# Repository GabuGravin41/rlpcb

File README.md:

# RL PCB — an AI design copilot for KiCad

RL PCB sits beside KiCad and works like a senior hardware engineer looking over your shoulder. You describe
what you want to build; it helps you choose real parts from your KiCad libraries, works out the values, places
the symbols for you, tells you **exactly** which pin connects to which pin, and then **checks your wiring**.
It also helps with the board: stackup, net classes, placement, routing guidance, autorouting and DRC.

**The division of labour is deliberate:** language models are bad at drawing schematics (floating "ghost"
wires, near-misses), so RL PCB never draws wires. You draw, and it does everything around the drawing:
research, parts, numbers, placement, instructions, and verification.

```
 you ──► "I need a 24 V PLC input card with 8 isolated inputs"
          │
 RL PCB ─►│ requirements → architecture → datasheet/app-note research → reference designs
          │ → parts from YOUR libraries → calculated values → design plan (parts + nets)
          │ → plan review (ERC before drawing) → symbols placed (no wires)
          │ → "wire U3 pin 7 (OUT) to R12 pin 1 …" → you wire → verify: 87 % done,
          │   R14.2 not connected, ghost wire at (120.6, 88.9) mm → fix → 100 %
          │ → stackup + net classes → placement → routing guidance / autoroute → DRC → Gerbers
```

## You choose how much the AI does

The engineer sets the AI's autonomy for each part of the design:

- **teach:** it explains.
- **advise:** it guides; you edit.
- **propose:** it prepares each change on a copy of the project, with the check results before and after, and you
  accept or reject it.
- **do:** it edits; every change is journalled and can be undone.

For example, the power block can be in "do" while the routing is in "advise". Every result says what the checks
verified and what they could not, such as part data without a datasheet or EMC that was not simulated, so a weaker
model's mistakes are caught where checks exist and flagged where they do not. See `docs/COPILOT.md`.

| Copilot tool | What it does |
|---|---|
| `copilot_status`, `copilot_mode` | Show or set the modes and scopes. |
| `proposals`, `proposal_show`, `proposal_accept`, `proposal_reject` | Review changes prepared on a copy. The chat panel has a Proposals button. |
| `undo`, `design_journal` | History of who changed what, in which mode; any change can be undone. |
| `assurance_report` | What is verified and what is not, before you order boards. |
| `kickoff`, `kickoff_apply` | From an idea to an architecture, questions, pitfalls and a project skeleton. |
| `explain_component`, `explain_net` | What a part or net does in this circuit, and why it is there. |
| `review_layout`, `compare_layouts` | Placement, routing, EMC and current-capacity review (IPC-2221 track widths against the plan's currents) with reasons; side-by-side layout studies. |
| `widen_power_tracks` | Widens the tracks of current-carrying nets as far as KiCad's DRC allows. |
| `interface_changes` | Notices between this board and the mechanical design (RL CAD). |

## What's inside

| Area | What it does |
|---|---|
| **Connectivity engine** | Computes nets from the drawing itself (pins, wires, junctions, labels, power symbols, hierarchical sheets, buses incl. bus aliases). Validated against KiCad's own netlister: **identical nets on all 13 KiCad 7 demo projects**, and on the KiCad 9/10 demos (Jetson Thor carrier, CM5, VME) it matches the boards' own netlists apart from stale/mechanical items. Reads KiCad 4/5 `.sch` too. |
| **Ghost-wire detector** | Dangling wire ends (with "near-miss: meant for U3 pin 7, 0.6 mm away"), floating wire groups, wire ends on the middle of another wire without a junction (KiCad treats these as *not connected*), labels touching nothing, off-grid pins, shorted power nets, misused no-connect flags. |
| **Library index** | SQLite/FTS search over every symbol and footprint in your KiCad libraries (stock + global + project tables, KiCad 7–10 incl. `.kicad_symdir`). Pins, footprint filters, pad counts, pitch. The AI never invents a part name. |
| **Design plan** | The agreed circuit (parts + nets + no-connects + requirements + decisions), stored in `<project>/.rlpcb/plan.json`. Pins can be named (`U1.VIN`, `U2.GND` → all GND pins, `U1.GPIO20` finds `IO20`). |
| **Plan review** | ERC for intent before drawing: unconnected power pins, floating inputs, output conflicts, missing decoupling, symbol/footprint pin-count mismatches. |
| **Symbol placement** | Groups each IC with the passives that serve it and lays them out around the pins they connect to (decoupling next to VCC, pull-up next to the output…), packs the groups on the sheet, grid-aligned, value & footprint set — **no wires**. Clipboard mode (Ctrl+V into the open editor) or file mode (with backups). Hierarchical sheets per block (`add_sheet`). Optional net labels exactly on pin ends for wide buses. |
| **Parts from anywhere** | Stock/global/project libraries; LCSC/JLCPCB parts converted on the fly (`import_lcsc_part C2040` → symbol + footprint + 3D, LCSC field set); symbols borrowed from open designs in the corpus; datasheets downloaded into the knowledge base (`fetch_datasheet`). |
| **Manufacturing** | Gerbers/drill/positions/STEP via kicad-cli; JLCPCB BOM + CPL (`export_jlcpcb`); plan fields (MPN, LCSC, voltage…) written back into drawn symbols (`sync_fields_from_plan`). |
| **Circuit blocks** | Pre-verified sub-circuits (buck, LDO, battery input, ADC divider, STM32F405 core, IMU, barometer, SPI flash, USB-C device, LED, connectors) with calculated values. MCUs connect by *function* (`SPI1_SCK`, `USART1_TX`, `USB_DP`) — the block knows the pins and refuses conflicts. The drone board rebuilt from 16 blocks verifies at 100 % with KiCad agreeing on every net. |
| **Design checks** | Engineering review beyond ERC: MCU pin functions, USB-C CC/data wiring, STM32 VCAP, TVS orientation, pin role vs net (swapped regulators), LED polarity, cap voltage ratings, inductor current, missing pull-ups, back-feed between supplies, nets that go nowhere, board fit; on the PCB: decoupling distance, crystal distance, track width vs current. |
| **Guided flow** | `next_step` reads the project and returns the single next action (with the exact tool call) plus a checklist — so smaller models (and beginners) don't get lost. |
| **Multi-board systems** | `system.json` with boards and harnesses: every cable pin pair checked (ground/power/voltage/TX↔RX/driver conflicts/open pins/pin count/per-pin current) plus the supply budget across boards. |
| **Wiring guide** | Per net: shortest wiring order (minimum spanning tree over the real pin coordinates), power symbols for rails, labels for far-apart pins, done/not-done per step. |
| **Verification** | Hand-drawn schematic vs plan: progress %, missing connections, shorts between planned nets, unplanned connections, wrong values/footprints, unplaced units, plus ghost wires. |
| **See the drawing** | Renders sheets to images and "pulls up" any section: zoomed crop around `U3, R7` with red highlight boxes. |
| **PCB tools** | Board overview & routing progress, stackup advisor (layer count from BGA pitch/interfaces/rails), net classes from the plan written into `.kicad_pro`, custom DRC rules, placement suggestions with target coordinates for every small passive (decoupling one cap per supply pin, pull-ups/load caps at their pin, two-sided, collision-free), footprint moves and flips (live or file), DRC, fabrication outputs. |
| **Routing** | Guidance by net class; Freerouting autorouting round-trip (DSN → router → SES, with a pure-Python SES importer) into a *copy* of your board; live track/via creation through the KiCad API for agreed simple routes. |
| **Live KiCad API** | KiCad 9/10 IPC API (kicad-python): highlight parts, read the selection, move footprints in one undo step, add tracks/vias, refill zones. |
| **Knowledge base** | ~35 dense engineering guides (power, decoupling/PDN, buck/boost, LDOs, BMS/UPS, high current, PLC I/O, motor drives, analog, EMC, stackups, SI, USB/Ethernet/PCIe/DDR, BGA & GPU-class boards, MCU/FPGA, RF, aerospace/high-rel, printers, DFM, KiCad workflow), 10 industry reference architectures (PLC, elevator, conveyor, humanoid joint, UPS, load sharing, printer mainboard, GPU accelerator, avionics, IoT), review/bring-up/fab checklists — plus **your own PDFs/books/datasheets** (`ingest_documents`). |
| **Reference corpus** | Ingests open-source KiCad projects (KiCad demos, GitHub repos, your folders; KiCad 4–10) and learns *how real designs wire each IC*: "how do others wire the DRV8302?" returns every pin's net and neighbours in the VESC design, with a consensus across designs. Seed list: Jetson Orin/Nano & Kria carriers, VESC, LibreSolar BMS/MPPT, LumenPnP, HackRF, Cynthion… |
| **Calculators** | IPC-2221 trace width, trace/via resistance & current, microstrip/stripline/differential impedance + width solver, critical length, skew, IPC-2221 clearance, E-series, feedback dividers, LED, RC, crystal load caps, buck/boost power stage, LDO thermal, MOSFET loss, PDN target impedance, capacitor SRF, shunts, thermal vias, wavelength. Every result shows the formula and caveats. |

## Three ways to talk to it

1. **Claude Desktop (works with your Claude Pro plan — no API key).** The installer registers RL PCB as an
   MCP server; open Claude Desktop and all 90 tools are available. Say *"Open my KiCad project in
   Documents\KiCad\myboard and help me design…"*.
2. **The RL PCB panel inside KiCad.** A toolbar button (PCB editor; also the schematic editor on KiCad 10)
   opens a chat panel. It needs either an Anthropic API key (Settings ⚙) or a local model through any
   OpenAI-compatible server (Ollama, LM Studio…).
3. **Claude Code / any MCP client:** `claude mcp add rlpcb -- <venv python> -m rlpcb.agent.mcp_server`.

## Install (Windows)

Requirements: KiCad 8, 9 or 10 (9/10 recommended), Python 3.10+, Git (for the corpus), optionally Java 21 for
autorouting.

```powershell
cd path\to\rlpcb
powershell -ExecutionPolicy Bypass -File .\install_windows.ps1            # add -SeedCorpus to download reference designs
```

It creates `.venv`, installs `mcp`, `kicad-python`, `pymupdf`, indexes your libraries, installs the KiCad
plugins into `Documents\KiCad\<version>\`, registers with Claude Desktop, makes a desktop shortcut, then runs
`python -m rlpcb doctor`.

Then in KiCad 9/10: **Preferences → Plugins → Enable KiCad API** (for live highlighting and moves) and restart.

Linux/macOS: `./install.sh [--seed-corpus]`.

## First session

```
You:     Open C:\Users\me\Documents\KiCad\plc_input and let's design an 8-channel 24 V digital input card
         for a Raspberry Pi CM5, IEC 61131-2 type 1, galvanically isolated.
RL PCB:  (asks about channel count, isolation voltage, connectors, power) … proposes architecture …
         searches the knowledge base (industrial_plc_io) and reference designs … calculates the input
         divider/current limiter … builds the plan … plan_review: 0 errors …
         places 41 symbols (Ctrl+V) … "Block 'input_ch1': 1) Draw a wire from J1 pin 1 at (25.4, 40.6) to
         R1 pin 1 at (38.1, 40.6) …"
You:     done with channel 1
RL PCB:  verify → 92 %: R3 pin 2 is not connected; the wire from U2 pin 3 ends 0.64 mm short of it
         (dangling end at 120.65, 88.90). Everything else in channel 1 matches the plan.
```

## Command line

```
python -m rlpcb doctor                    # check everything
python -m rlpcb index [--force]           # (re)index libraries
python -m rlpcb check  path\to\project    # ghost wires & drawing problems
python -m rlpcb verify path\to\project    # schematic vs plan
python -m rlpcb nets   path\to\project [regex]
python -m rlpcb ingest-docs D:\Books\Electronics
python -m rlpcb corpus seed | owner/repo | D:\OpenHardware
python -m rlpcb tool <tool_name> '{"json": "args"}'
python -m rlpcb serve --open              # chat panel
python -m rlpcb mcp                       # MCP server (stdio)
```

## Safety of your files

- Schematic/board edits are *splices*: the rest of the file stays byte-for-byte identical, the result is parsed
  before writing, and a timestamped backup goes to `<project>\.rlpcb\backups\`.
- If KiCad has the file open (lock file present), RL PCB warns you; clipboard mode and the live API avoid the
  conflict entirely.
- The autorouter writes `<name>.routed.kicad_pcb`, never your original.
- `mech_export` writes `<board>.mech.json`, which describes the board for the product around it: outline, holes, connectors with the edge they face, and part heights. `mech_check` checks the board against the `enclosure.json` that RL CAD writes. See `../rlcad/docs/INTEGRATION.md`.
- `finish_routing` closes what the autorouter left (plane stitching, grid router, rip-up, negotiated congestion) and writes `<name>.finished.kicad_pcb`, checked with KiCad's own DRC after every step.
- The panel server only listens on 127.0.0.1 and rejects cross-origin requests. `allow_file_writes=false` in
  Settings makes RL PCB read-only.

## Honest limits (and the roadmap)

- It will not draw wires, by design. Net labels on pin ends are offered for buses.
- The AI's design judgement is only as good as its research: it cites the knowledge base, the datasheet section
  and real reference designs, and you should still read the datasheet's typical-application circuit.
- Autorouting is for non-critical nets; power loops, high-speed and analog nets should be routed by hand with
  the guidance given.
- A Blackwell-class accelerator board (20+ layer HDI, ~1000 A core rail, PCIe Gen5/6) is not a first project;
  the `gpu_accelerator_board` architecture file lays out a realistic learning path toward it.

See `docs/EVALUATION.md` for how a small model performs with and without blocks, `examples/drone_fc/` for a complete worked project (a drone flight controller, idea → routed board), `docs/USER_GUIDE.md` for the workflow in depth and `docs/ARCHITECTURE.md` for how it works.

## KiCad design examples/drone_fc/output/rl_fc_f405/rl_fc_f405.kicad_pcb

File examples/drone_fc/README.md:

# Worked example: a drone flight controller, from idea to routed board

This is what a new project looks like with RL PCB. Every step below is a real tool call. `design_session.py`
and `board_session.py` are the exact sequence the copilot runs, so you can replay it.

**Brief:** a 5-inch-quad flight controller, 36×36 mm, 30.5 mm M3 mounting, 2–6S LiPo input, Betaflight-style pinout.

| Stage | What RL PCB did | Result |
|---|---|---|
| Requirements → architecture | Recorded requirements + decisions in the plan: STM32F405 (the Betaflight/INAV reference MCU), TPS5430 buck 5 V/3 A → AP2112K 3.3 V LDO, IMU on its own ferrite-filtered rail, SIG/GND/PWR/SIG stackup | `.rlpcb/plan.json` |
| Parts | 61 parts, all from the stock KiCad libraries (symbol + footprint pin counts checked) | 0 invented parts |
| Numbers | Feedback divider 9.31 k/3.01 k → 4.998 V; crystal loads 2·(12−3) = 18 pF; VBAT divider 10 k/1 k → 25.2 V reads 2.29 V; buck L ≈ 13.4 µH → 15 µH, Isat > 3 A | shown with formulas |
| Plan review (ERC before drawing) | Power pins, floating inputs, output conflicts, decoupling, no-connects | **0 errors, 0 warnings** |
| Placement (schematic) | 4 hierarchical sheets (Power / MCU / Sensors / Connectors); each IC placed with its passives beside the pins they serve. **No wires.** | `img/1_schematic_mcu_sheet.png` |
| Wiring guide | Per net: power symbols for rails, global labels for nets that cross sheets, shortest wire order for the rest (e.g. *"Draw a wire from U1.8 (PH) at (78.74, 45.72) to C3.2 at (93.98, 40.64)"*) | step list |
| Verify | Hand-drawn schematic vs plan | 100 % of 174 connections; KiCad's own netlister agrees (79/79 nets) |
| Mistake detection | Swapped SDA/SCL on the baro, and a label dropped 0.64 mm short of a pin | *"Planned nets I2C1_SCL, I2C1_SDA are connected together…"*, *"global label 'SPI1_MISO' is not attached…; nearest pin is U4.4 (SAO/SD0) 0.64 mm away"* |
| Stackup + net classes | 4 layers (density 5 parts/cm², USB 90 Ω); 6 net classes, 32 patterns written to `.kicad_pro` | |
| Board placement | You (or the copilot) place ~20 anchor parts from the plan's layout notes; `placement_suggestions` puts the 40 passives next to the pins they serve (MCU decoupling one cap per VDD pin, load caps at the crystal, pull-ups at the pin), 22 parts on the bottom side | 0 courtyard overlaps; a second pass is a no-op |
| Autoroute (Freerouting, 3 min) | Routes a *copy* of the board | 88–91 % routed across runs, 0 clearance errors from routing; 17–22 connections left for you |
| DRC | Remaining errors are all footprint-inherent: 0.5 mm-pitch LGA pads vs the 0.2 mm default clearance (set Default clearance to 0.15 mm, since JLC allows 0.1), the USB-C's own NPTH tabs, and one via 0.03 mm too close to the edge | |

## What *you* still do (by design)

1. **Draw the wires.** RL PCB never draws them. Follow the wiring guide, then say "verify".
2. **Press F8** (Update PCB from Schematic). In the cloud demo, `make_board.py` stands in for F8.
3. **Route the critical nets by hand before autorouting:** the buck hot loop (C1–U1–D1), the switch node,
   USB D+/D−, and the IMU SPI. Then lock them, autoroute the rest, and finish the last ~10 % by hand.
4. **Read the datasheet sections the copilot points at.** In this design:
   - ICM-20602 RESV pins: the symbol marks them reserved, but check the datasheet for any that must be tied to GND or VDDIO.
   - SMAJ28A: this library symbol names its pins A1/A2, so the plan uses pin numbers. Confirm the cathode faces VBAT.
   - SRP7028A-150M: confirm Isat ≥ 3 A. (L1 was downsized from a 12.5 mm part so it fits on a 36 mm board.)
   - USB-only power: 5 V can back-feed the VBAT rail through the TPS5430 high-side body diode when no battery is
     connected. Many flight controllers accept this; add a diode or load switch if your ESC must stay unpowered.

## Finishing the board (fabrication-ready)

The autorouted copy above still had open connections, so the board was finished for manufacture:

1. **Design rules set for JLCPCB 4-layer**: 0.13 mm default clearance (0.15 mm power/analog, 0.2 mm VBAT), 0.15 mm
   signal tracks, 0.4 mm power, 1.0 mm VBAT, 0.6/0.3 mm vias (0.5/0.3 mm around the IMU), 0.3 mm copper-to-edge.
2. **Freerouting with In1 (GND) and In2 (+3V3) as planes only**: the bottom GND pour was left out of the router's
   input, because the router treated it as a plane and left bottom-side GND pads "connected" to islands that do not
   exist once KiCad fills the pour. Three passes (14 + 8 + 7 min on 2 cores) left 5 connections.
3. **`rlpcb.pcb.finish`** (new) closed the rest with KiCad's own geometry and DRC after every step:
   plane stitching (stub + via from a pad to its plane), a 4-layer grid router with vias, rip-up and retry, and a
   negotiated-congestion router (PathFinder-style) for the two knots: the IMU's SPI fan-out under the MCU, and the
   BMP280 corner. Dangling stubs and an edge-violating via were removed; the USB-C shield pads connect solid.

Result (`output/rl_fc_f405/rl_fc_f405.kicad_pcb`, KiCad DRC): **0 errors, 0 unconnected pads**, 239 pad-to-net
assignments identical to the plan. Remaining warnings: 52 silkscreen overlaps, 22 silk over copper, 2 silk at the
board edge (cosmetic; the fab clips silk on pads), and library-path notices from the machine it was routed on.
52 short segments run on the inner plane layers (24 on In1, 28 on In2). Check the GND return path under the IMU SPI
lines if you care about the last dB of noise.

### Power-stage rework after the layout review

`review_layout` later found real problems in the routed board above, which DRC could not see because they are about
current and loop area, not spacing:

- **Switch node:** the buck's switch node (BUCK_SW, 2.5 A) was 22 mm of 0.15 mm track that wound under the
  regulator. At that current, IPC-2221 puts the rise at roughly 250 °C, and the long loop radiates. The cause was
  that `setup_netclasses` sized nets only by their declared class, so a switch node with a current but no class got
  the 0.15 mm default. It now sizes every net that has a current.
- **+5V rail:** the 2 A rail ran 0.4 mm on the inner layers. Part of it ran on In1 (the GND plane), which also cut
  the ground plane.

The rework, done with RL PCB's own tools (placement, grid router, `widen_power_tracks`, KiCad DRC after each step):

- U1 is turned 180°, so its PH pin faces the catch diode and the inductor. L1 moves 0.85 mm left.
- The switch node is now one 6 × 9 mm copper pour joining U1 PH, the bootstrap capacitor, D1 and L1.
- The input capacitor C1 sits at the VIN pin, with its ground in a small pour tied to the regulator's thermal pad
  and the planes.
- The feedback divider (R1, R2) moves next to the FB pin. It senses the output through a thin trace.
- C5 (22 µF) moves under L1's output as the buck's output capacitor; C4 stays at the LDO.
- +5V leaves the inner layers. A 1.0 mm trunk runs on B.Cu to the LDO and receiver corner, and a 0.8 mm branch runs
  to the VTX connector.
- The rest of the +5V and VBAT copper is widened as far as DRC allows.

After the rework, `review_layout` reports no power concerns (it had three). DRC is still 0 errors and 0 unconnected
pads, and the Gerbers, drill, positions, STEP, CPL and `mech.json` are regenerated.

Two points are left for the engineer:

- **USB pair length mismatch (10.4 mm):** this stays as it is. USB_DP and USB_DM leave the ESD clamp in the opposite
  order to the one in which they arrive at the MCU, so routing them side by side needs a crossing. At USB full speed
  (12 Mb/s, the F405's OTG_FS) this mismatch does not affect the data. The clean fix is a schematic change: swap the
  clamp's two channels (USBLC6-2 channels are interchangeable), then route both lines together.
- **VBAT width:** the plan gives VBAT 3 A, which leaves its 1.0 mm tracks at about 17 °C rise. The board itself draws
  well under 2 A from the battery, so check the plan's figure before widening further.

Manufacturing files are in `output/rl_fc_f405/fab/`: Gerbers + drill (+ drill map) for the 4 copper layers,
`positions.csv`, and `jlcpcb/` BOM + CPL with LCSC numbers. Five BOM lines have no LCSC number on purpose:
J1 (battery pads) and J6 (SWD pads) are not assembled; L1 (SRP7028A-150M), R2 (3.01 k 1 %) and Y1 (8 MHz 3225,
CL = 12 pF to match the 18 pF load caps) must be picked at order time or supplied.

## Replay it

```bash
python examples/drone_fc/design_session.py  C:\work            # plan, review, sheets, placement, wiring guide
python examples/drone_fc/design_session.py  C:\work --labels   # demo only: simulate a finished drawing
# open C:\work\rl_fc_f405 in KiCad, wire it (or use --labels), press F8, save
python examples/drone_fc/board_session.py   C:\work\rl_fc_f405 --route
```

Or just ask in the chat panel / Claude Desktop: *"Design a 30.5 mm flight controller with an F405, ICM-20602,
BMP280, blackbox flash and a 2–6S input"*. The copilot runs these same tools and stops to ask you at each decision.

## The generated project

`output/rl_fc_f405/` is the result of the replay, saved in KiCad 7 format (KiCad 8/9/10 upgrade it when you open it).
It contains:

- the 4-sheet schematic with pin labels (the simulated drawing);
- `rl_fc_f405.kicad_pcb`, the finished, routed board (DRC clean);
- `rl_fc_f405.placed.kicad_pcb`, the placed board before routing;
- `fab/`, the manufacturing files;
- `.rlpcb/plan.json`, the design plan, so you can open the project and ask RL PCB about any part or net.

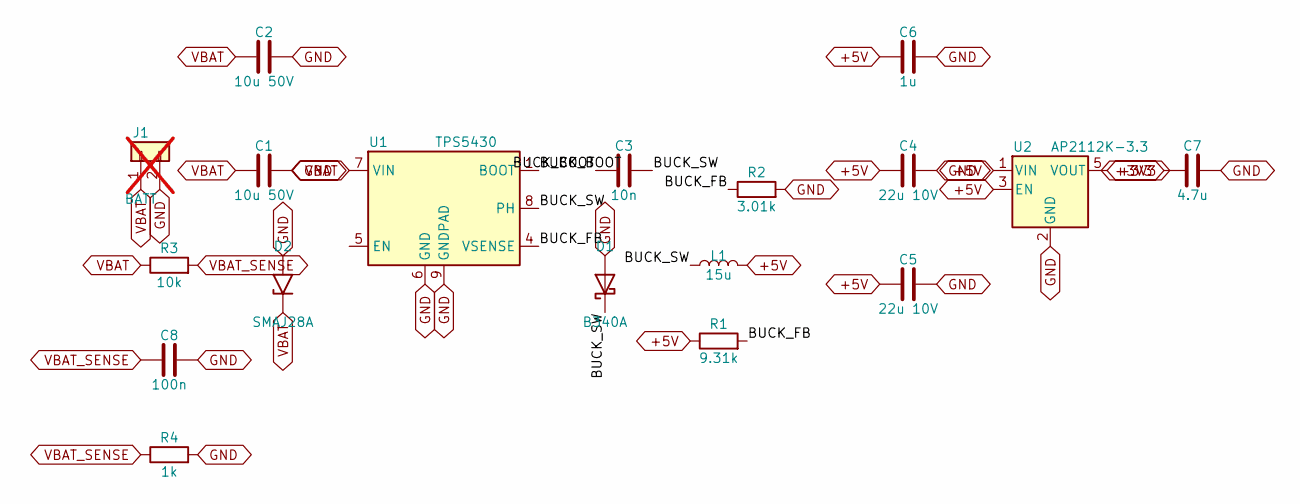
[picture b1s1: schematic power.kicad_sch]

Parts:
C1, C2: 10u 50V; C_1206_3216Metric; MPN CL31A106KBHNNNE; LCSC C13585
C3: 10n; C_0402_1005Metric; MPN CL05B103KB5NNNC; LCSC C15195
C4, C5: 22u 10V; C_0805_2012Metric; MPN CL21A226MAQNNNE; LCSC C45783
C6: 1u; C_0402_1005Metric; MPN CL05A105KA5NQNC; LCSC C52923
C7: 4.7u; C_0603_1608Metric; MPN CL10A475KO8NNNC; LCSC C19666
C8: 100n; C_0402_1005Metric; MPN CL05B104KO5NNNC; LCSC C1525
D1: B340A; D_SMA; MPN B340A-13-F; LCSC C85098
D2: SMAJ28A; D_SMA; MPN SMAJ28A-13-F; LCSC C134977
J1: BATT; SolderWire-1.5sqmm_1x02_P6mm_D1.7mm_OD3mm; not fitted
L1: 15u; L_Bourns_SRP7028A_7.3x6.6mm; MPN SRP7028A-150M
R1: 9.31k; R_0402_1005Metric; MPN RNCF0402BKE9K31; LCSC C4174801
R2: 3.01k; R_0402_1005Metric
R3: 10k; R_0402_1005Metric; MPN 0402WGF1002TCE; LCSC C25744
R4: 1k; R_0402_1005Metric; MPN 0402WGF1001TCE; LCSC C11702
U1: TPS5430; TI_SO-PowerPAD-8_ThermalVias; MPN TPS5430DDAR; LCSC C9864
U2: AP2112K-3.3; SOT-23-5; MPN AP2112K-3.3TRG1; LCSC C51118

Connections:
+3V3: C7.1, U2.5 (VOUT); also elsewhere on the board
+5V: C4.1, C5.1, C6.1, L1.2, R1.1, U2.1 (VIN), U2.3 (EN); also elsewhere on the board
/Power/BUCK_BOOT: C3.1, U1.1 (BOOT)
/Power/BUCK_FB: R1.2, R2.1, U1.4 (VSENSE)
/Power/BUCK_SW: C3.2, D1.1 (K), L1.1, U1.8 (PH)
GND: C1.2, C2.2, C4.2, C5.2, C6.2, C7.2, C8.2, D1.2 (A), D2.2 (A2), J1.2, R2.2, R4.2, U1.6 (GND), U1.9 (GNDPAD), U2.2 (GND); also elsewhere on the board
VBAT: C1.1, C2.1, D2.1 (A1), J1.1, R3.1, U1.7 (VIN); also elsewhere on the board
VBAT_SENSE: C8.1, R3.2, R4.1; also elsewhere on the board

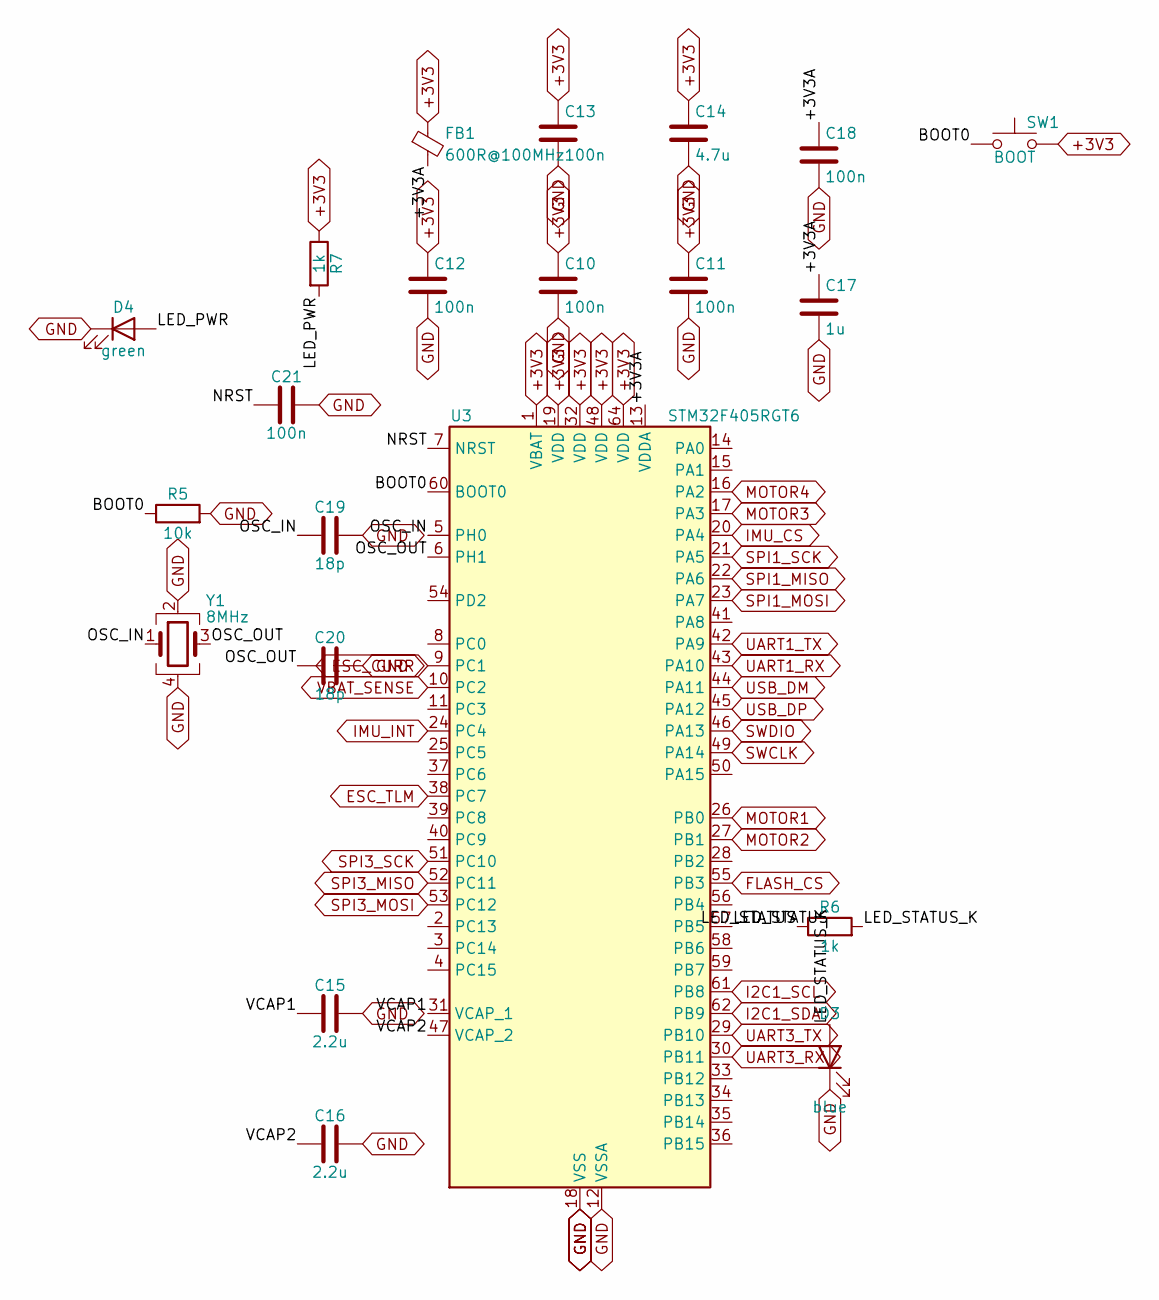
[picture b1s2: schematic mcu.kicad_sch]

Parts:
C10, C11, C12, C13, C18, C21: 100n; C_0402_1005Metric; MPN CL05B104KO5NNNC; LCSC C1525
C14: 4.7u; C_0603_1608Metric; MPN CL10A475KO8NNNC; LCSC C19666
C15, C16: 2.2u; C_0402_1005Metric; MPN CL05A225MQ5NSNC; LCSC C12530
C17: 1u; C_0402_1005Metric; MPN CL05A105KA5NQNC; LCSC C52923
C19, C20: 18p; C_0402_1005Metric; MPN 0402CG180J500NT; LCSC C1549
D3: blue; LED_0603_1608Metric; MPN KT-0603B; LCSC C2288
D4: green; LED_0603_1608Metric; MPN KT-0603G; LCSC C12624
FB1: 600R@100MHz; L_0603_1608Metric; MPN GZ1608D601TF; LCSC C1002
R5: 10k; R_0402_1005Metric; MPN 0402WGF1002TCE; LCSC C25744
R6, R7: 1k; R_0402_1005Metric; MPN 0402WGF1001TCE; LCSC C11702
SW1: BOOT; SW_SPST_TL3342; MPN TL3342F160QG; LCSC C2886898
U3: STM32F405RGT6; LQFP-64_10x10mm_P0.5mm; MPN STM32F405RGT6; LCSC C15742
Y1: 8MHz; Crystal_SMD_3225-4Pin_3.2x2.5mm

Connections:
+3V3: C10.1, C11.1, C12.1, C13.1, C14.1, FB1.1, R7.1, SW1.2, U3.1 (VBAT), U3.19 (VDD), U3.32 (VDD), U3.48 (VDD), U3.64 (VDD); also elsewhere on the board
/MCU/+3V3A: C17.1, C18.1, FB1.2, U3.13 (VDDA)
/MCU/BOOT0: R5.1, SW1.1, U3.60 (BOOT0)
/MCU/LED_PWR: D4.2 (A), R7.2
/MCU/LED_STATUS: R6.1, U3.57 (PB5)
/MCU/LED_STATUS_K: D3.2 (A), R6.2
/MCU/NRST: C21.1, U3.7 (NRST)
/MCU/OSC_IN: C19.1, U3.5 (PH0), Y1.1
/MCU/OSC_OUT: C20.1, U3.6 (PH1), Y1.3
/MCU/VCAP1: C15.1, U3.31 (VCAP_1)
/MCU/VCAP2: C16.1, U3.47 (VCAP_2)
ESC_CURR: U3.9 (PC1); also elsewhere on the board
ESC_TLM: U3.38 (PC7); also elsewhere on the board
FLASH_CS: U3.55 (PB3); also elsewhere on the board
GND: C10.2, C11.2, C12.2, C13.2, C14.2, C15.2, C16.2, C17.2, C18.2, C19.2, C20.2, C21.2, D3.1 (K), D4.1 (K), R5.2, U3.12 (VSSA), U3.18 (VSS), U3.63 (VSS), Y1.2, Y1.4; also elsewhere on the board
I2C1_SCL: U3.61 (PB8); also elsewhere on the board
I2C1_SDA: U3.62 (PB9); also elsewhere on the board
IMU_CS: U3.20 (PA4); also elsewhere on the board
IMU_INT: U3.24 (PC4); also elsewhere on the board
MOTOR1: U3.26 (PB0); also elsewhere on the board
MOTOR2: U3.27 (PB1); also elsewhere on the board
MOTOR3: U3.17 (PA3); also elsewhere on the board
MOTOR4: U3.16 (PA2); also elsewhere on the board
SPI1_MISO: U3.22 (PA6); also elsewhere on the board
SPI1_MOSI: U3.23 (PA7); also elsewhere on the board
SPI1_SCK: U3.21 (PA5); also elsewhere on the board
SPI3_MISO: U3.52 (PC11); also elsewhere on the board
SPI3_MOSI: U3.53 (PC12); also elsewhere on the board
SPI3_SCK: U3.51 (PC10); also elsewhere on the board
SWCLK: U3.49 (PA14); also elsewhere on the board
SWDIO: U3.46 (PA13); also elsewhere on the board
UART1_RX: U3.43 (PA10); also elsewhere on the board
UART1_TX: U3.42 (PA9); also elsewhere on the board
UART3_RX: U3.30 (PB11); also elsewhere on the board
UART3_TX: U3.29 (PB10); also elsewhere on the board
USB_DM: U3.44 (PA11); also elsewhere on the board
USB_DP: U3.45 (PA12); also elsewhere on the board
VBAT_SENSE: U3.10 (PC2); also elsewhere on the board

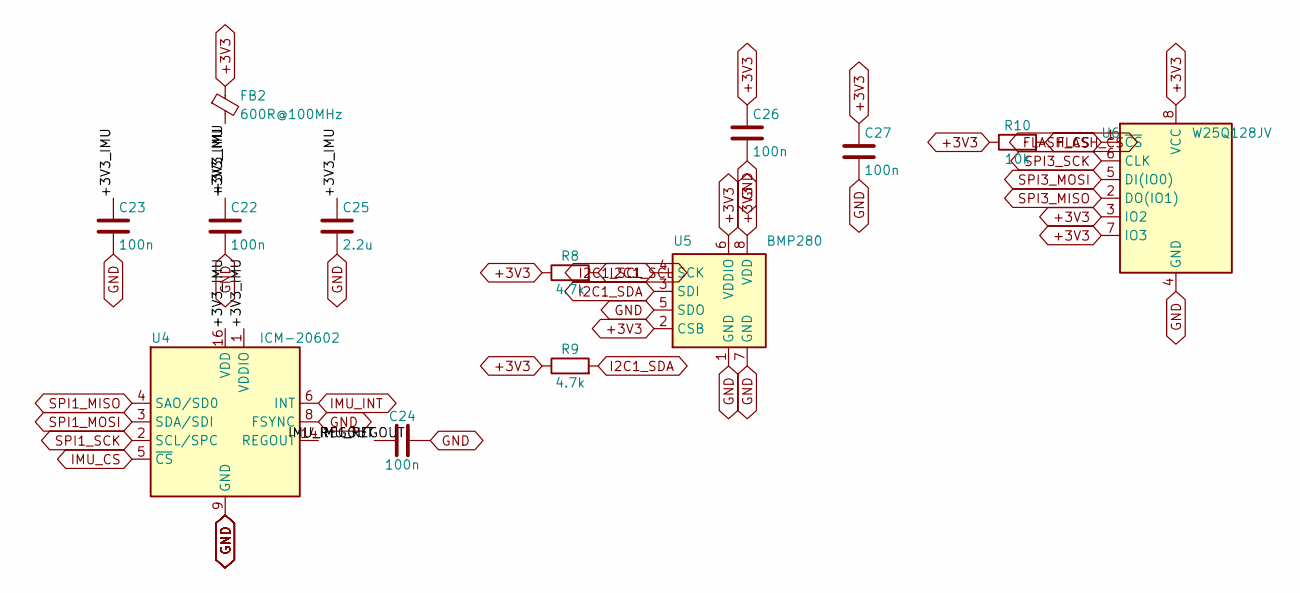
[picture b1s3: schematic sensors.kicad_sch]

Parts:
C22, C23, C24, C26, C27: 100n; C_0402_1005Metric; MPN CL05B104KO5NNNC; LCSC C1525
C25: 2.2u; C_0402_1005Metric; MPN CL05A225MQ5NSNC; LCSC C12530
FB2: 600R@100MHz; L_0603_1608Metric; MPN GZ1608D601TF; LCSC C1002
R8, R9: 4.7k; R_0402_1005Metric; MPN 0402WGF4701TCE; LCSC C25900
R10: 10k; R_0402_1005Metric; MPN 0402WGF1002TCE; LCSC C25744
U4: ICM-20602; LGA-16_3x3mm_P0.5mm_LayoutBorder3x5y; MPN ICM-20602; LCSC C97633
U5: BMP280; Bosch_LGA-8_2x2.5mm_P0.65mm_ClockwisePinNumbering; MPN BMP280; LCSC C83291
U6: W25Q128JV; SOIC-8_5.23x5.23mm_P1.27mm; MPN W25Q128JVSIQ; LCSC C97521

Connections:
+3V3: C26.1, C27.1, FB2.1, R8.1, R9.1, R10.1, U5.2 (CSB), U5.6 (VDDIO), U5.8 (VDD), U6.3 (IO2), U6.7 (IO3), U6.8 (VCC); also elsewhere on the board
/Sensors/+3V3_IMU: C22.1, C23.1, C25.1, FB2.2, U4.1 (VDDIO), U4.16 (VDD)
/Sensors/IMU_REGOUT: C24.1, U4.14 (REGOUT)
FLASH_CS: R10.2, U6.1 (~CS); also elsewhere on the board
GND: C22.2, C23.2, C24.2, C25.2, C26.2, C27.2, U4.8 (FSYNC), U4.9 (GND), U4.10 (GND), U4.11 (GND), U4.12 (GND), U4.13 (GND), U4.15 (GND), U5.1 (GND), U5.5 (SDO), U5.7 (GND), U6.4 (GND); also elsewhere on the board
I2C1_SCL: R8.2, U5.4 (SCK); also elsewhere on the board
I2C1_SDA: R9.2, U5.3 (SDI); also elsewhere on the board
IMU_CS: U4.5 (~CS); also elsewhere on the board
IMU_INT: U4.6 (INT); also elsewhere on the board
SPI1_MISO: U4.4 (SAO/SD0); also elsewhere on the board
SPI1_MOSI: U4.3 (SDA/SDI); also elsewhere on the board
SPI1_SCK: U4.2 (SCL/SPC); also elsewhere on the board
SPI3_MISO: U6.2 (DO(IO1)); also elsewhere on the board
SPI3_MOSI: U6.5 (DI(IO0)); also elsewhere on the board
SPI3_SCK: U6.6 (CLK); also elsewhere on the board

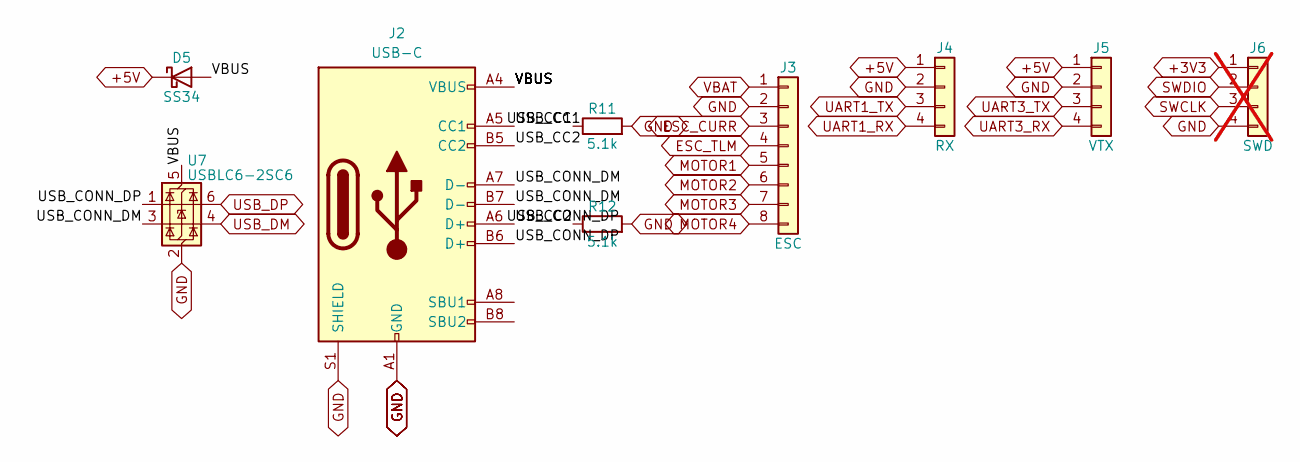
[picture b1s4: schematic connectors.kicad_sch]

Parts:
D5: SS34; D_SMA; MPN SS34; LCSC C8678
J2: USB-C; USB_C_Receptacle_GCT_USB4105-xx-A_16P_TopMnt_Horizontal; MPN USB4105-GF-A; LCSC C3020560
J3: ESC; JST_SH_SM08B-SRSS-TB_1x08-1MP_P1.00mm_Horizontal; MPN SM08B-SRSS-TB(LF)(SN); LCSC C160407
J4: RX; JST_SH_SM04B-SRSS-TB_1x04-1MP_P1.00mm_Horizontal; MPN SM04B-SRSS-TB(LF)(SN); LCSC C160404
J5: VTX; JST_SH_SM04B-SRSS-TB_1x04-1MP_P1.00mm_Horizontal; MPN SM04B-SRSS-TB(LF)(SN); LCSC C160404
J6: SWD; PinHeader_1x04_P1.27mm_Vertical; not fitted
R11, R12: 5.1k; R_0402_1005Metric; MPN 0402WGF5101TCE; LCSC C25905
U7: USBLC6-2SC6; SOT-23-6; MPN USBLC6-2SC6; LCSC C7519

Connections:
+3V3: J6.1; also elsewhere on the board
+5V: D5.1 (K), J4.1, J5.1; also elsewhere on the board
/Connectors/USB_CC1: J2.A5 (CC1), R11.1
/Connectors/USB_CC2: J2.B5 (CC2), R12.1
/Connectors/USB_CONN_DM: J2.A7 (D-), J2.B7 (D-), U7.3 (I/O2)
/Connectors/USB_CONN_DP: J2.A6 (D+), J2.B6 (D+), U7.1 (I/O1)
/Connectors/VBUS: D5.2 (A), J2.A4 (VBUS), J2.A9 (VBUS), J2.B4 (VBUS), J2.B9 (VBUS), U7.5 (VBUS)
ESC_CURR: J3.3; also elsewhere on the board
ESC_TLM: J3.4; also elsewhere on the board
GND: J2.A1 (GND), J2.A12 (GND), J2.B1 (GND), J2.B12 (GND), J2.S1 (SHIELD), J3.2, J4.2, J5.2, J6.4, R11.2, R12.2, U7.2 (GND); also elsewhere on the board
MOTOR1: J3.5; also elsewhere on the board
MOTOR2: J3.6; also elsewhere on the board
MOTOR3: J3.7; also elsewhere on the board
MOTOR4: J3.8; also elsewhere on the board
SWCLK: J6.3; also elsewhere on the board
SWDIO: J6.2; also elsewhere on the board
UART1_RX: J4.4; also elsewhere on the board
UART1_TX: J4.3; also elsewhere on the board
UART3_RX: J5.4; also elsewhere on the board
UART3_TX: J5.3; also elsewhere on the board
USB_DM: U7.4 (I/O2); also elsewhere on the board
USB_DP: U7.6 (I/O1); also elsewhere on the board
VBAT: J3.1; also elsewhere on the board

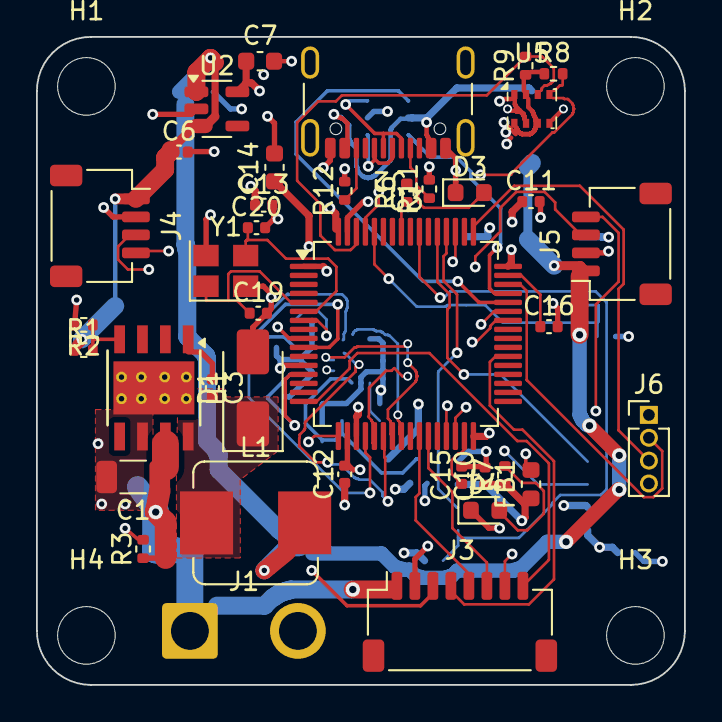
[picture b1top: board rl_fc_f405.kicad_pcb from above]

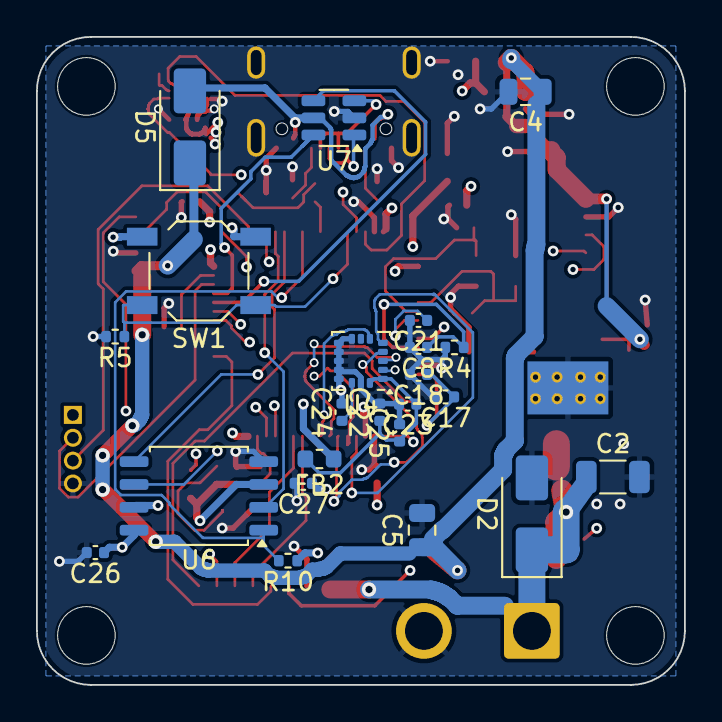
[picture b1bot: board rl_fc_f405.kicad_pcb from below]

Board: 4 copper layers, 36.0 x 36.0 mm, 65 parts (23 on the bottom side), 50 nets.

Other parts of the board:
H1, H2, H3, H4: MountingHole_3.2mm_M3

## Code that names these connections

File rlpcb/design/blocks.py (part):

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A block is a parameterised sub-circuit whose internal wiring, part choices and values have been checked once (against
the datasheet's typical application and by building a board with it). A model using blocks only chooses blocks, sets a
few parameters and connects *ports* — e.g. ``{"VOUT": "+5V", "GND": "GND"}``, or for an MCU peripheral functions
such as ``{"SPI1_SCK": "IMU_SCK", "USART1_TX": "RX_TX"}`` instead of pin numbers. That removes most of the places a
weaker model can go wrong: pin names, decoupling, feedback networks, crystal loads, alternate-function pins.

Every block returns the calculations it made (with formulas) and the datasheet points a human should still confirm.
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# =============================================================================== MCU
# STM32F405RGTx: default alternate-function pin for each peripheral signal (LQFP-64).
F405_FUNCTIONS = {
    "USB_DM": "PA11", "USB_DP": "PA12", "SWDIO": "PA13", "SWCLK": "PA14",
    "SPI1_SCK": "PA5", "SPI1_MISO": "PA6", "SPI1_MOSI": "PA7",
    "SPI2_SCK": "PB13", "SPI2_MISO": "PB14", "SPI2_MOSI": "PB15",
    "SPI3_SCK": "PC10", "SPI3_MISO": "PC11", "SPI3_MOSI": "PC12",
    "I2C1_SCL": "PB8", "I2C1_SDA": "PB9", "I2C2_SCL": "PB10", "I2C2_SDA": "PB11",
    "USART1_TX": "PA9", "USART1_RX": "PA10", "USART2_TX": "PA2", "USART2_RX": "PA3",
    "USART3_TX": "PB10", "USART3_RX": "PB11", "UART4_TX": "PA0", "UART4_RX": "PA1",
    "USART6_TX": "PC6", "USART6_RX": "PC7",
    "TIM3_CH1": "PB4", "TIM3_CH2": "PB5", "TIM3_CH3": "PB0", "TIM3_CH4": "PB1",
    "TIM5_CH3": "PA2", "TIM5_CH4": "PA3", "TIM8_CH1": "PC6", "TIM8_CH2": "PC7", "TIM4_CH1": "PB6", "TIM4_CH2": "PB7",
    "CAN1_RX": "PB8", "CAN1_TX": "PB9",
    "ADC_IN0": "PA0", "ADC_IN1": "PA1", "ADC_IN4": "PA4", "ADC_IN8": "PB0", "ADC_IN9": "PB1",
    "ADC_IN10": "PC0", "ADC_IN11": "PC1", "ADC_IN12": "PC2", "ADC_IN13": "PC3", "ADC_IN14": "PC4", "ADC_IN15": "PC5",
}
# Every pin that can carry each function on the STM32F405 LQFP-64 (datasheet AF table, common peripherals).
F405_AF = {
    "USB_DP": {"PA12"}, "USB_DM": {"PA11"}, "SWDIO": {"PA13"}, "SWCLK": {"PA14"},
    "SPI1_SCK": {"PA5", "PB3"}, "SPI1_MISO": {"PA6", "PB4"}, "SPI1_MOSI": {"PA7", "PB5"},
    "SPI2_SCK": {"PB10", "PB13"}, "SPI2_MISO": {"PB14", "PC2"}, "SPI2_MOSI": {"PB15", "PC3"},
    "SPI3_SCK": {"PC10", "PB3"}, "SPI3_MISO": {"PC11", "PB4"}, "SPI3_MOSI": {"PC12", "PB5"},
    "I2C1_SCL": {"PB6", "PB8"}, "I2C1_SDA": {"PB7", "PB9"}, "I2C2_SCL": {"PB10"}, "I2C2_SDA": {"PB11"},
    "I2C3_SCL": {"PA8"}, "I2C3_SDA": {"PC9"},
    "USART1_TX": {"PA9", "PB6"}, "USART1_RX": {"PA10", "PB7"}, "USART2_TX": {"PA2"}, "USART2_RX": {"PA3"},
    "USART3_TX": {"PB10", "PC10"}, "USART3_RX": {"PB11", "PC11"}, "UART4_TX": {"PA0", "PC10"}, "UART4_RX": {"PA1", "PC11"},
    "UART5_TX": {"PC12"}, "UART5_RX": {"PD2"}, "USART6_TX": {"PC6"}, "USART6_RX": {"PC7"},
    "CAN1_RX": {"PB8", "PA11"}, "CAN1_TX": {"PB9", "PA12"}, "CAN2_RX": {"PB5", "PB12"}, "CAN2_TX": {"PB6", "PB13"},
}
# generic net-name tokens → the set of function names that satisfy them
F405_GENERIC = {
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}
MCU_AF = {"MCU_ST_STM32F4:STM32F405RGTx": (F405_AF, F405_GENERIC)}

F405_GPIO = [f"P{b}{i}" for b, n in (("A", 16), ("B", 16), ("C", 16)) for i in range(n)] + ["PD2", "PH0", "PH1"]
F405_RESERVED = {"PH0", "PH1", "PA13", "PA14"}  # HSE crystal and SWD (used by the block itself)


@block("stm32f405_core", "STM32F405RGT6 core (168 MHz Cortex-M4F, LQFP-64)", "mcu",
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        "boot_button": {"default": True, "desc": "Add a BOOT0 push-button (hold at power-up for USB DFU)"}},
       "Four 100 nF + 4.7 µF on VDD, 2×2.2 µF VCAP, ferrite + 1 µF/100 nF on VDDA, HSE crystal with calculated load "
       "caps, NRST filter, BOOT0 pull-down (+ button). Connect peripherals by function name (SPI1_SCK, USART1_TX, "
       "USB_DP, ADC_IN12, TIM3_CH3…) or any GPIO name (PB5). Unused GPIOs get no-connect flags.")
def _f405(hse_mhz=8, crystal_cl_pf=12, boot_button=True):
    lc = F.crystal_load_caps(cl_pf=float(crystal_cl_pf))
    cl = lc["nearest_E12_pf"]
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                       "Hold at power-up for the USB DFU bootloader"))
    nets = [("VCAP1", ["U.VCAP_1", "CVCAP1.1"], {}), ("VCAP2", ["U.VCAP_2", "CVCAP2.1"], {}),
            ("VDDA", ["FB.2", "U.VDDA", "CA1.1", "CA2.1"], {"net_class": "analog"}),
            ("OSC_IN", ["U.PH0", "Y.1", "CX1.1"], {}), ("OSC_OUT", ["U.PH1", "Y.3", "CX2.1"], {}),
            ("NRST", ["U.NRST", "CRST.1"], {}), ("BOOT0", ["U.BOOT0", "RBOOT.1"] + (["SW.1"] if boot_button else []), {})]
    vdd = ["U.VDD", "U.VBAT", "FB.1", "CBULK.1"] + [f"CD{i}.1" for i in range(1, 5)] + (["SW.2"] if boot_button else [])
    gnd = ["U.VSS", "U.VSSA", "CBULK.2", "CVCAP1.2", "CVCAP2.2", "CA1.2", "CA2.2", "Y.2", "Y.4", "CX1.2", "CX2.2",
           "CRST.2", "RBOOT.2"] + [f"CD{i}.2" for i in range(1, 5)]
    ports = {"VDD": Port(vdd, "power_in", desc="3.3 V supply", net_attrs={"net_class": "power"}),
             "GND": Port(gnd, "ground", default_net="GND", net_attrs={"net_class": "ground"}),
             "SWDIO": Port(["U.PA13"], "signal", required=False), "SWCLK": Port(["U.PA14"], "signal", required=False),
             "NRST": Port(["U.NRST"], "signal", required=False, desc="Reset (for a debug connector)")}
    # any GPIO, and function aliases, are optional ports; resolved in _mcu_port()
    return BlockBuild(parts, nets, ports, calculations=[{"crystal_load_caps": lc}],
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                               "Check every function→pin choice against the reference manual's alternate-function table "
                               "if you use peripherals beyond the ones listed by list_blocks."],
                      layout="One 100 nF per VDD pin, on the same side, < 2 mm away; crystal + load caps within 5 mm of "
                             "PH0/PH1 with ground pour under them; VCAP caps at their pins.")


BLOCK_GPIO = {"stm32f405_core": (F405_FUNCTIONS, F405_GPIO, F405_RESERVED)}
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            pin = funcs.get(port.upper()) or (port.upper() if port.upper() in gpios else None)
            if pin is None:
                problems.append(f"'{port}' is not a port of {block_id}: use a function name ({', '.join(sorted(funcs)[:8])}…) "
                                "or a GPIO name like PB5")
                connect.pop(port)
                continue
            if pin in reserved and port.upper() not in ("SWDIO", "SWCLK"):
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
